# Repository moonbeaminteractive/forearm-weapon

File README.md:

# Original Design

# Forearm-weapon
long range weapon on the forearm

### Parts:</br>
3d printed parts</br>
2 Rubber Bands</br>
1 Single Turn 3/8" Square Cermet 10k Potentiometer</br>
1" Google Cardboard lens for IR tube</br>
IR LED</br>
Arduino Mini Pro</br>
Wire</br>
3.3v Laser Pointer module</br>

# Gauntlet

### Features:</br>
1.The shape of gauntlet is symmetrical which could fit both left-handed and right-handed users.</br>
2.The gauntlet is adjustable by using elastic robber band and velcro.</br>
3.The shape of gauntlet is simple so that potential users are able to cut various soft metarial easily with scissors instead of using laser cut machine. </br>
4.Gauntlet itself actually indicates identity of the player as a "warrior".</br>

# Usage

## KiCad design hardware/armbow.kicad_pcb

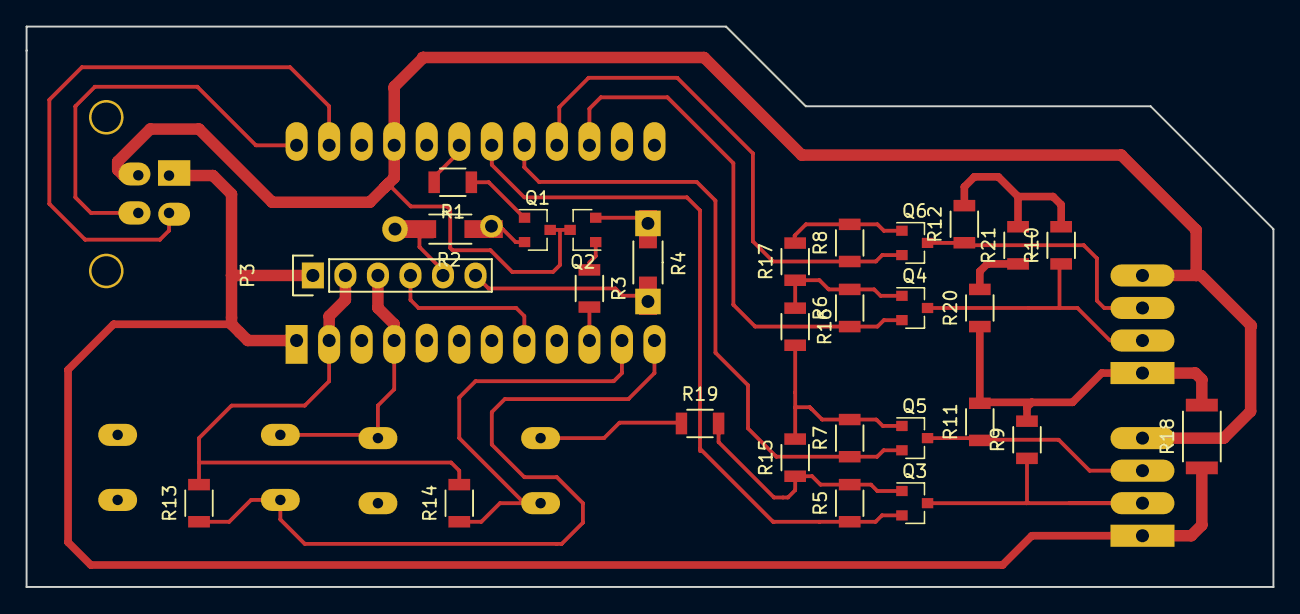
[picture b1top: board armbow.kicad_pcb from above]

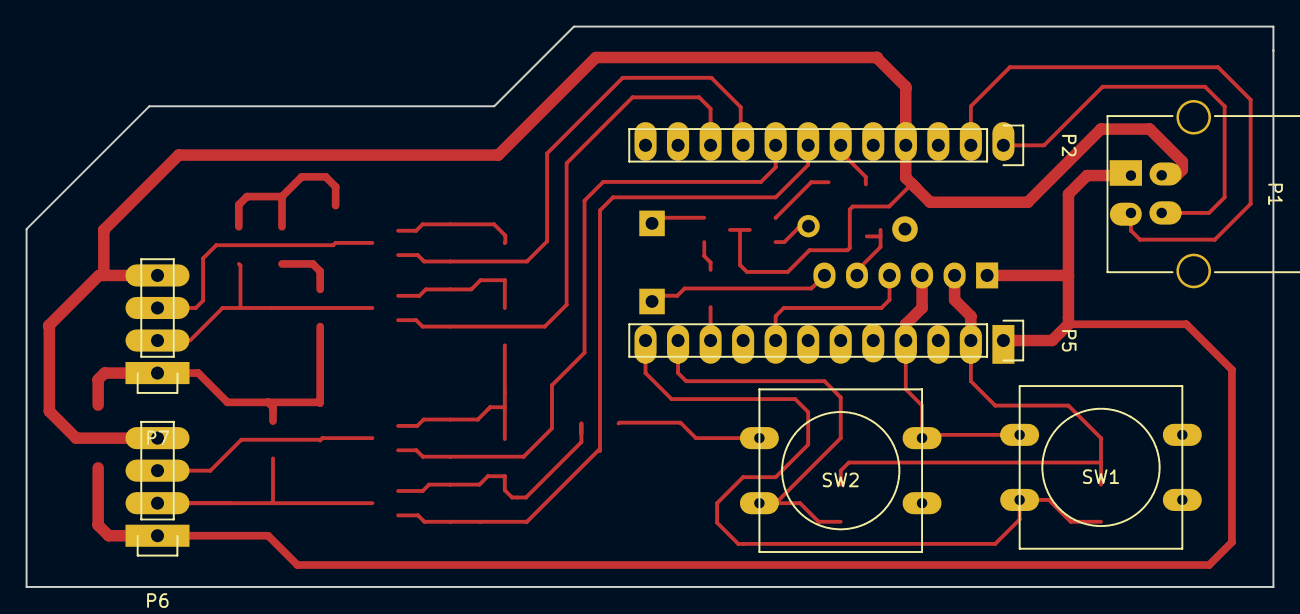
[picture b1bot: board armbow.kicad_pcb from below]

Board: 2 copper layers, 97.3 x 43.8 mm, 35 parts (7 on the bottom side), 24 nets.

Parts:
P1: USB_B_TOVEST; USB_B
P2, P5: CONN_01X12; Pin_Header_Straight_1x12
P3: To_Bow_Connection; Pin_Header_Straight_1x06
P6: RECHARGE_DOTSTART; Pin_Header_Straight_1x04
P7: ARROWS_DOTSTART; Pin_Header_Straight_1x04
Q1, Q2: PZT2222A; SOT-23
Q3, Q4, Q5, Q6: BSS138; SOT-23
R1, R3, R9, R10, R11, R12: 1K; R_1206
R2: 10; Resistor_SMD+THTuniversal_1206_RM10_HandSoldering
R4: 50; Resistor_SMD+THTuniversal_1206_RM10_HandSoldering
R5, R6, R7, R8, R13, R14: 10K; R_1206
R15, R16, R17, R19, R20, R21: 0; R_1206
R18: 0; R_2010
SW1, SW2: SW_PUSH; SW_PUSH-12mm

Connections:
A0: P3.4, P5.8
ARROW_CLOCK_IN: P7.2, Q4.3, R10.1
ARROW_DATA_IN: P7.3, Q6.3, R12.1
CATH_IRLED: P3.5, R2.2
CATH_Laser: P3.6, R4.2
D3: P2.6, R1.2
D4: P2.7, Q3.2, R5.1
D5: P2.8, Q5.2, R7.1
D6: P2.9, Q6.2, R8.1
D7: P2.10, Q4.2, R6.1
D10: P5.12, R13.1, SW1.1
D11: P5.11, R14.1, SW2.1
D12: P5.10, R3.2
GND: P1.4, P2.4, P3.2, P5.2, P6.4, P7.4, Q1.3, Q2.3, R13.2, R14.2
unnamed: Q1.1, R1.1
unnamed: Q1.2, R2.1
unnamed: Q2.1, R3.1
unnamed: Q2.2, R4.1
RECHARGE_CLOCK_IN: P6.2, Q3.3, R9.1
RECHARGE_DATA_IN: P6.3, Q5.3, R11.1
RX(Weapon): P1.2, P2.2
TX(Weapon): P1.3, P2.1
V33: P3.3, P5.4, Q3.1, Q4.1, Q5.1, Q6.1, R5.2, R6.2, R7.2, R8.2, R15.1, R15.2, R16.1, R16.2, R17.1, R17.2, R19.1, R19.2, SW1.2, SW2.2
V50: P1.1, P3.1, P5.1, P6.1, P7.1, R9.2, R10.2, R11.2, R12.2, R18.1, R18.2, R20.1, R20.2, R21.1, R21.2

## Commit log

2016-11-13 added folders
2016-11-13 replaced gitignore with empty txt
2016-11-21 Added Model of Bow and Diagram
2016-11-21 Added parts list and Diagram to show how it works
2016-12-12 New Models and Printer code as well as firmware
    Added models to print flat with better mechanisms for firing and code to
    trigger the shots and laser
2016-12-13 edit IRled code
2016-12-13 add lib
2016-12-13 add dotstar
2016-12-14 Added kicad files for guantlet controller
2016-12-14 final modifications and gerber files created for armbow pcb
2016-12-16 edit communication
2016-12-17 Added parts for arm case and assembly picture
2016-12-17 Update README.md
    Added assembly diagram
